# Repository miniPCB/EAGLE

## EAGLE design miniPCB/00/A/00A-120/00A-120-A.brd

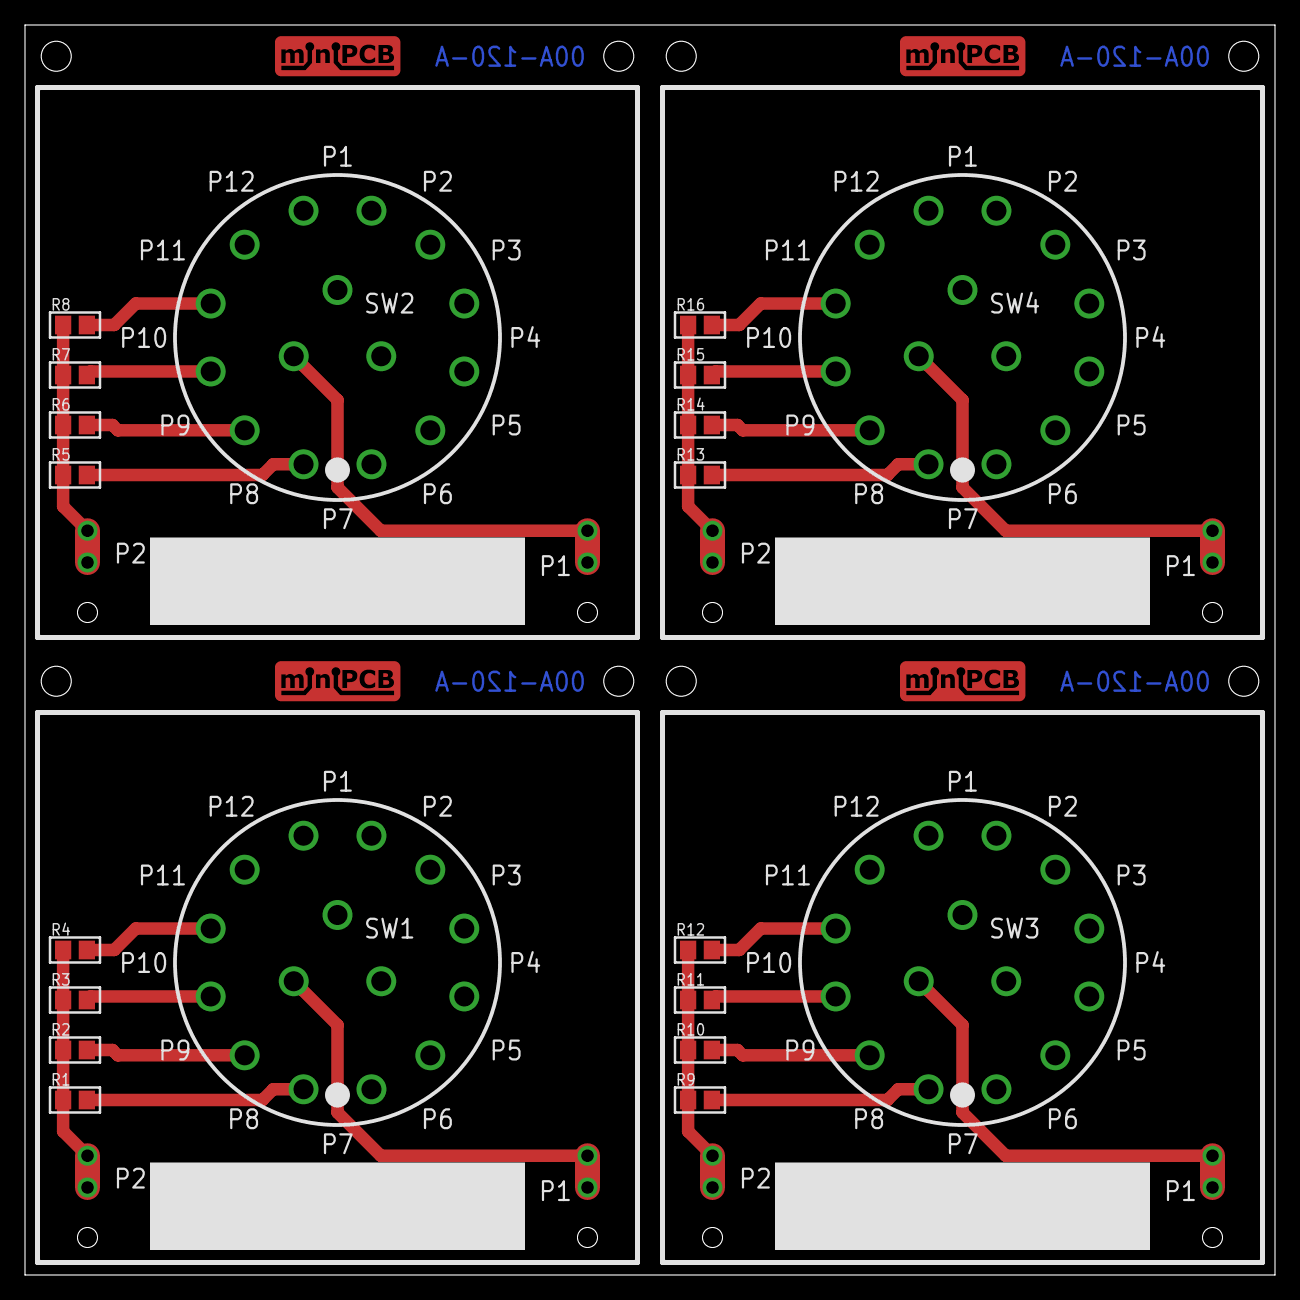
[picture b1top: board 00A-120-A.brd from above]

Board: 2 copper layers, 100.0 x 100.0 mm, 33 parts (0 on the bottom side), 24 nets.

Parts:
E$1: MINIPCB_PANEL_IMAGEFRAME
P1, P2, P3, P4, P5, P6, P7, P8: PINS_1_1MM-NOTEXT
PCB1, PCB2, PCB3, PCB4: MINIPCB_0P_50X50MM
R1, R2, R3, R4, R5, R6, R7, R8, R9, R10, R11, R12, R13, R14, R15, R16: R0805
SW1, SW2, SW3, SW4: SWITCH-ROTARY-3P4T

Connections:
unnamed: P1.1, P1.2, SW1.A
unnamed: R1.2, SW1.1
unnamed: R2.2, SW1.2
unnamed: R3.2, SW1.3
unnamed: R4.2, SW1.4
unnamed: P3.1, P3.2, SW2.A
unnamed: R5.2, SW2.1
unnamed: R6.2, SW2.2
unnamed: R7.2, SW2.3
unnamed: R8.2, SW2.4
unnamed: P4.1, P4.2, R5.1, R6.1, R7.1, R8.1
unnamed: P5.1, P5.2, SW3.A
unnamed: R9.2, SW3.1
unnamed: P2.1, P2.2, R1.1, R2.1, R3.1, R4.1
unnamed: R10.2, SW3.2
unnamed: R11.2, SW3.3
unnamed: R12.2, SW3.4
unnamed: P6.1, P6.2, R9.1, R10.1, R11.1, R12.1
unnamed: P7.1, P7.2, SW4.A
unnamed: R13.2, SW4.1
unnamed: R14.2, SW4.2
unnamed: R15.2, SW4.3
unnamed: R16.2, SW4.4
unnamed: P8.1, P8.2, R13.1, R14.1, R15.1, R16.1
